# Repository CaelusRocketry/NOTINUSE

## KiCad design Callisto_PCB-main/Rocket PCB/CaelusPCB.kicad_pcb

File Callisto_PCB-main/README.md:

# Callisto_PCB

### Code Description
- `Caelus PCB`: backups of CaelusPCB repo.
- `Comms` (Arduino/Teensy based)
  - `Comms/fakeDataLB/fakeDataLB.ino` generates "fake" 16 switch readings and sends it over UART/Serial communications (LB to GPCB). It also translates each of the switch states into a 4 letter hex string. 
  - `Comms/fakeDataLB/toGPCB.ino` takes the 4 digit hex number send from the UART communications from LB and parses it into 16 integers, which could be 16 valves to swtich.

(there are 16 switches to serve as buffer in the case we wish to expand the number of valves we wish to toggle, although we may not use that many.)

- `Rocket PCB`: KiCad diagrams of the PCB to be placed in the Rocket.

- `twowaycomm` (Raspberry Pi based): testing of wireless two way communications between two Raspberry Pis.
  - `twowaycomm/main0.py` is code to be run on the **sender** Raspberry Pi.
    - **HOWEVER** we may run this on a windows computer for testing, in which case `twowaycomm/main0-ON WIN.py` should be used.
  - `twowaycomm/main1.py` is code to be run on the **receiver** Raspberry Pi, which will send an "acknowledgement" message to the sender raspberry pi.
  - `twowaycomm/main.py` is the combination of `twowaycomm/main0.py` and `twowaycomm/main1.py` into a single file.

The sender Rapsberry Pi represents the Ground Station, and the receiver Raspberry Pi represents the Test Stand or GPCB.

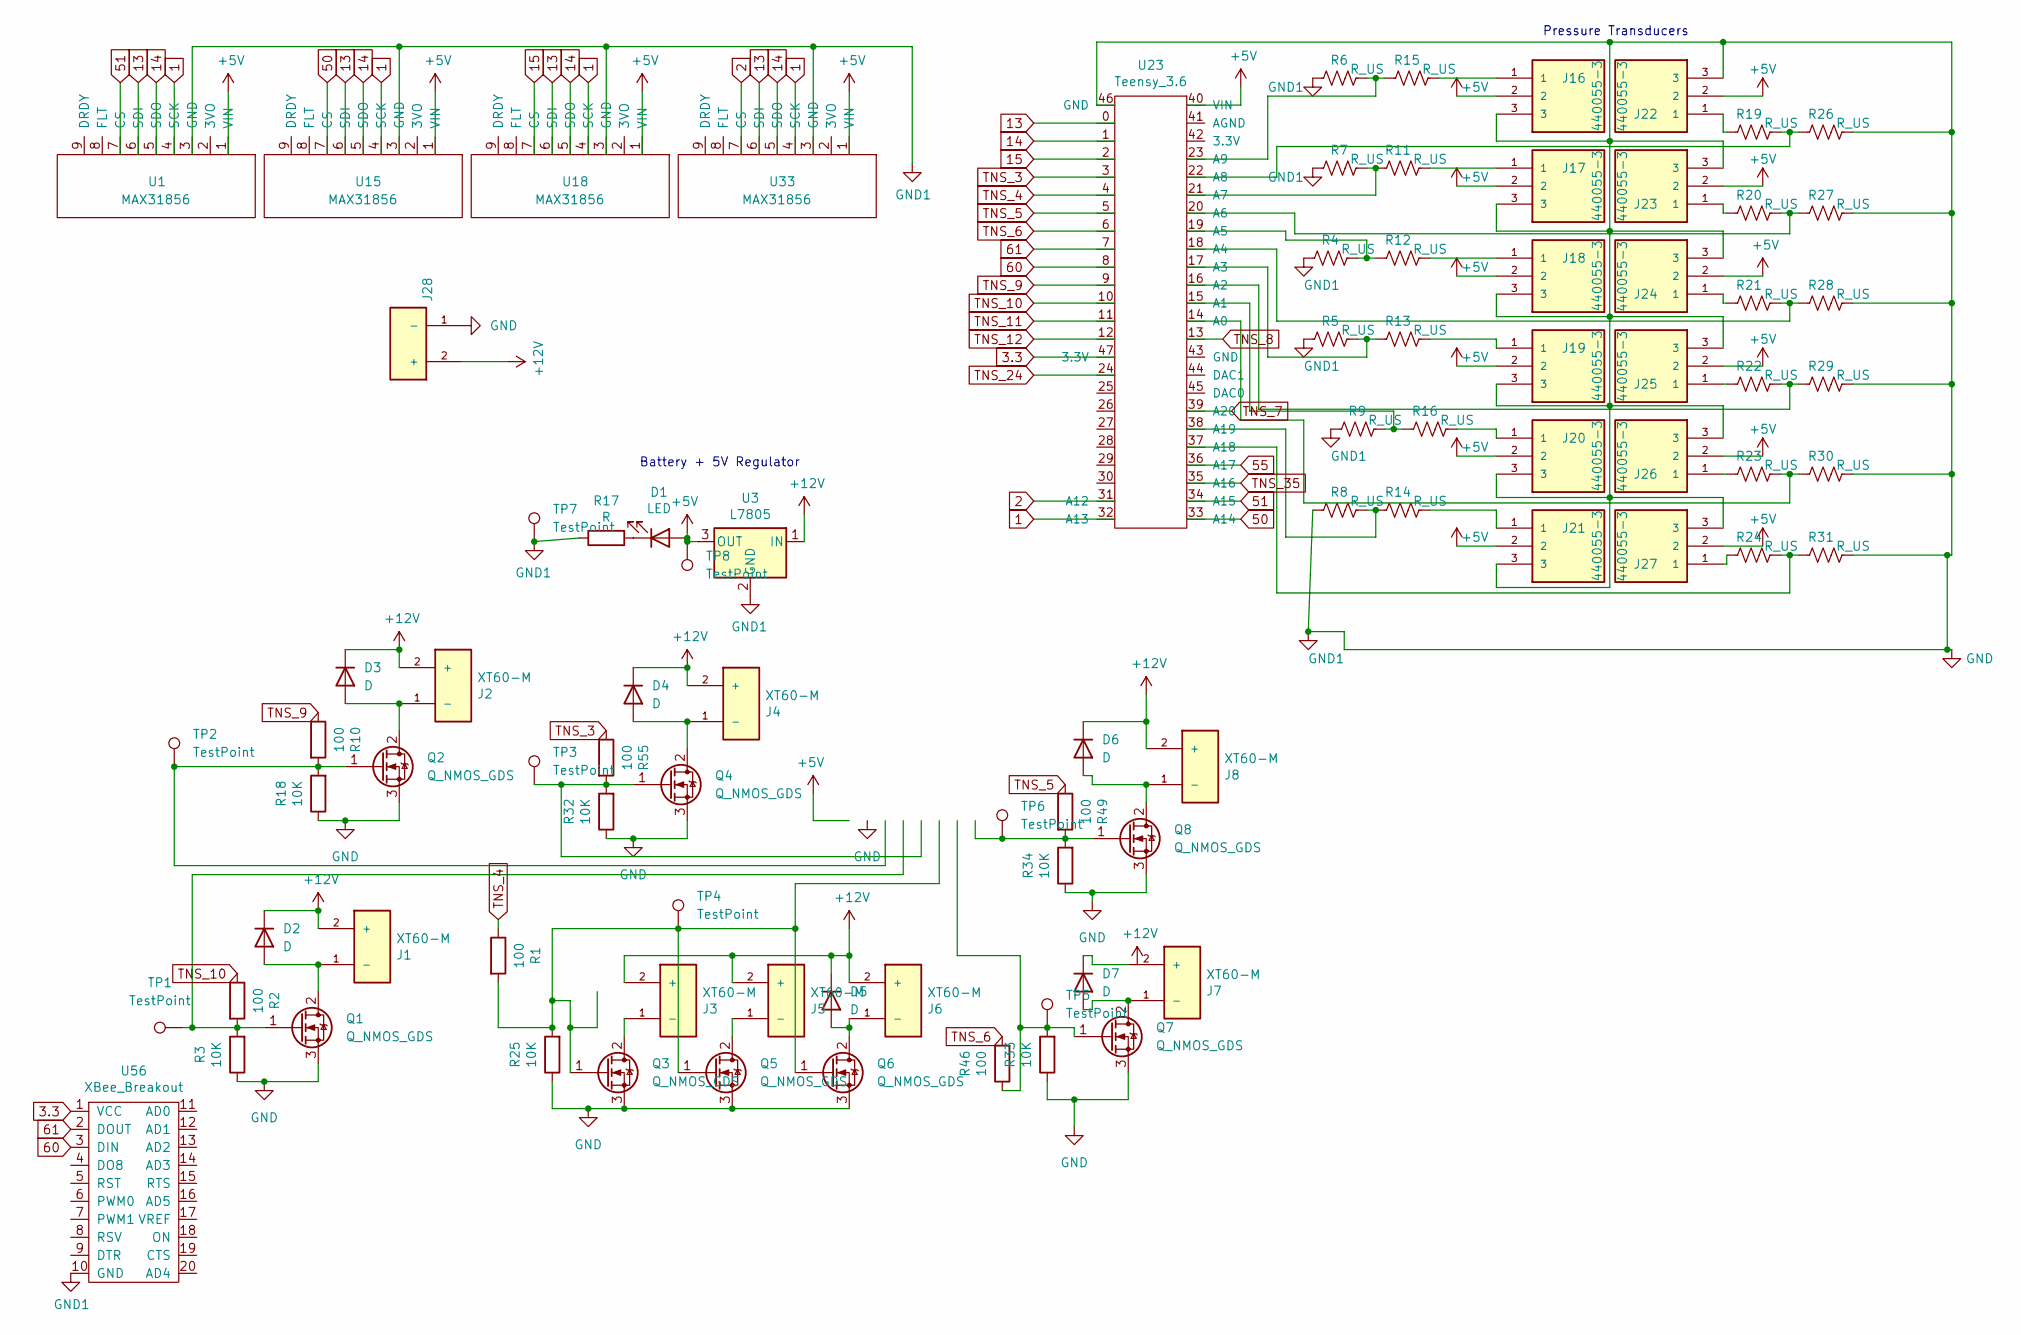
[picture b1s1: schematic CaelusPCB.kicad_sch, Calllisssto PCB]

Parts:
D1: LED; LED_D5.0mm
D2, D3, D4, D5, D6, D7: D; D_A-405_P2.54mm_Vertical_AnodeUp
J1, J2, J3, J4, J5, J6, J7, J8: XT60-M; AMASS_XT60-M; PARTREV 1.2
J16, J17, J18, J19, J20, J21, J22, J23, J24, J25, J26, J27: 440055-3; Crimp_Header
J28: CaelusPCB-rescue_XT60-M-CaelusPCB; AMASS_XT60-M; PARTREV 1.2
Q1, Q2, Q3, Q4, Q5, Q6, Q7, Q8: Q_NMOS_GDS; TO-220-3_Vertical
R1, R2, R10, R46, R49, R55: 100; R_Axial_DIN0309_L9.0mm_D3.2mm_P12.70mm_Horizontal
R3, R18, R25, R32, R33, R34: 10K; R_Axial_DIN0309_L9.0mm_D3.2mm_P12.70mm_Horizontal
R4, R5, R6, R7, R8, R9, R11, R12, R13, R14, R15, R16, R19, R20, R21, R22, R23, R24, R26, R27, R28, R29, R30, R31: R_US; R_Axial_DIN0309_L9.0mm_D3.2mm_P12.70mm_Horizontal
R17: R; R_Axial_DIN0309_L9.0mm_D3.2mm_P12.70mm_Horizontal
TP1, TP2, TP3, TP4, TP5, TP6, TP7, TP8: TestPoint; TestPoint_THTPad_D2.0mm_Drill1.0mm
U1, U15, U18, U33: MAX31856
U3: L7805; TO-220-3_Horizontal_TabDown
U23: Teensy_3.6
U56: XBee_Breakout; Xbee_Breakout

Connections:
1: U1.4 (SCK), U15.4 (SCK), U18.4 (SCK), U23.32 (A13), U33.4 (SCK)
2: U23.31 (A12), U33.7 (CS)
3.3: U23.47 (3.3V), U56.1 (VCC)
13: U1.6 (SDI), U15.6 (SDI), U18.6 (SDI), U23.0, U33.6 (SDI)
14: U1.5 (SDO), U15.5 (SDO), U18.5 (SDO), U23.1, U33.5 (SDO)
15: U18.7 (CS), U23.2
50: U15.7 (CS), U23.33 (A14)
51: U1.7 (CS), U23.34 (A15)
55: U23.36 (A17)
60: U23.8, U56.3 (DIN)
61: U23.7, U56.2 (DOUT)
+5V: D1.2 (A), J16.2, J17.2, J18.2, J19.2, J20.2, J21.2, J22.2, J23.2, J24.2, J25.2, J26.2, J27.2, TP8.1, U1.1 (VIN), U3.3 (OUT), U15.1 (VIN), U18.1 (VIN), U23.40 (VIN), U33.1 (VIN)
+12V: D2.1 (K), D3.1 (K), D4.1 (K), D5.1 (K), D6.1 (K), J1.2 (+), J2.2 (+), J3.2 (+), J4.2 (+), J5.2 (+), J6.2 (+), J8.2 (+), J28.2 (+), U3.1 (IN)
GND: J16.3, J17.3, J18.3, J19.3, J20.3, J21.3, J22.3, J23.3, J24.3, J25.3, J26.3, J27.3, J28.1 (-), Q1.3 (S), Q2.3 (S), Q3.3 (S), Q4.3 (S), Q5.3 (S), Q6.3 (S), Q7.3 (S), Q8.3 (S), R3.1, R4.1, R5.1, R6.1, R7.1, R8.1, R9.1, R17.1, R18.1, R25.1, R26.2, R27.2, R28.2, R29.2, R30.2, R31.2, R32.1, R33.1, R34.1, TP7.1, U1.3 (GND), U3.2 (GND), U15.3 (GND), U18.3 (GND), U23.46 (GND), U33.3 (GND), U56.10 (GND)
unnamed: D1.1 (K), R17.2
unnamed: D2.2 (A), J1.1 (-), Q1.2 (D)
unnamed: D3.2 (A), J2.1 (-), Q2.2 (D)
unnamed: D4.2 (A), J4.1 (-), Q4.2 (D)
unnamed: D5.2 (A), J6.1 (-), Q6.2 (D)
unnamed: D6.2 (A), J8.1 (-), Q8.2 (D)
unnamed: D7.1 (K), J7.2 (+)
unnamed: D7.2 (A), J7.1 (-), Q7.2 (D)
unnamed: J3.1 (-), Q3.2 (D)
unnamed: J5.1 (-), Q5.2 (D)
unnamed: J16.1, R15.2
unnamed: J17.1, R11.2
unnamed: J18.1, R12.2
unnamed: J19.1, R13.2
unnamed: J20.1, R16.2
unnamed: J21.1, R14.2
unnamed: J22.1, R19.1
unnamed: J23.1, R20.1
unnamed: J24.1, R21.1
unnamed: J25.1, R22.1
unnamed: J26.1, R23.1
unnamed: J27.1, R24.1
unnamed: Q1.1 (G), R2.2, R3.2, TP1.1
unnamed: Q2.1 (G), R10.2, R18.2, TP2.1
unnamed: Q3.1 (G), Q5.1 (G), Q6.1 (G), R1.2, R25.2, TP4.1
unnamed: Q4.1 (G), R32.2, R55.2, TP3.1
unnamed: Q7.1 (G), R33.2, R46.1, TP5.1
unnamed: Q8.1 (G), R34.2, R49.2, TP6.1
unnamed: R7.2, R11.1, U23.21 (A7)
unnamed: R4.2, R12.1, U23.19 (A5)
unnamed: R5.2, R13.1, U23.17 (A3)
unnamed: R8.2, R14.1, U23.38 (A19)
unnamed: R6.2, R15.1, U23.23 (A9)
unnamed: R9.2, R16.1, U23.15 (A1)
unnamed: R19.2, R26.1, U23.22 (A8)
unnamed: R20.2, R27.1, U23.20 (A6)
unnamed: R21.2, R28.1, U23.18 (A4)
unnamed: R22.2, R29.1, U23.16 (A2)
unnamed: R23.2, R30.1, U23.14 (A0)
unnamed: R24.2, R31.1, U23.37 (A18)
TNS_3: R55.1, U23.3
TNS_4: R1.1, U23.4
TNS_5: R49.1, U23.5
TNS_6: R46.2, U23.6
TNS_7: U23.39 (A20)
TNS_8: U23.13
TNS_9: R10.1, U23.9
TNS_10: R2.1, U23.10
TNS_11: U23.11
TNS_12: U23.12
TNS_24: U23.24
TNS_35: U23.35 (A16)

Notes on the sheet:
Battery + 5V Regulator
Pressure Transducers

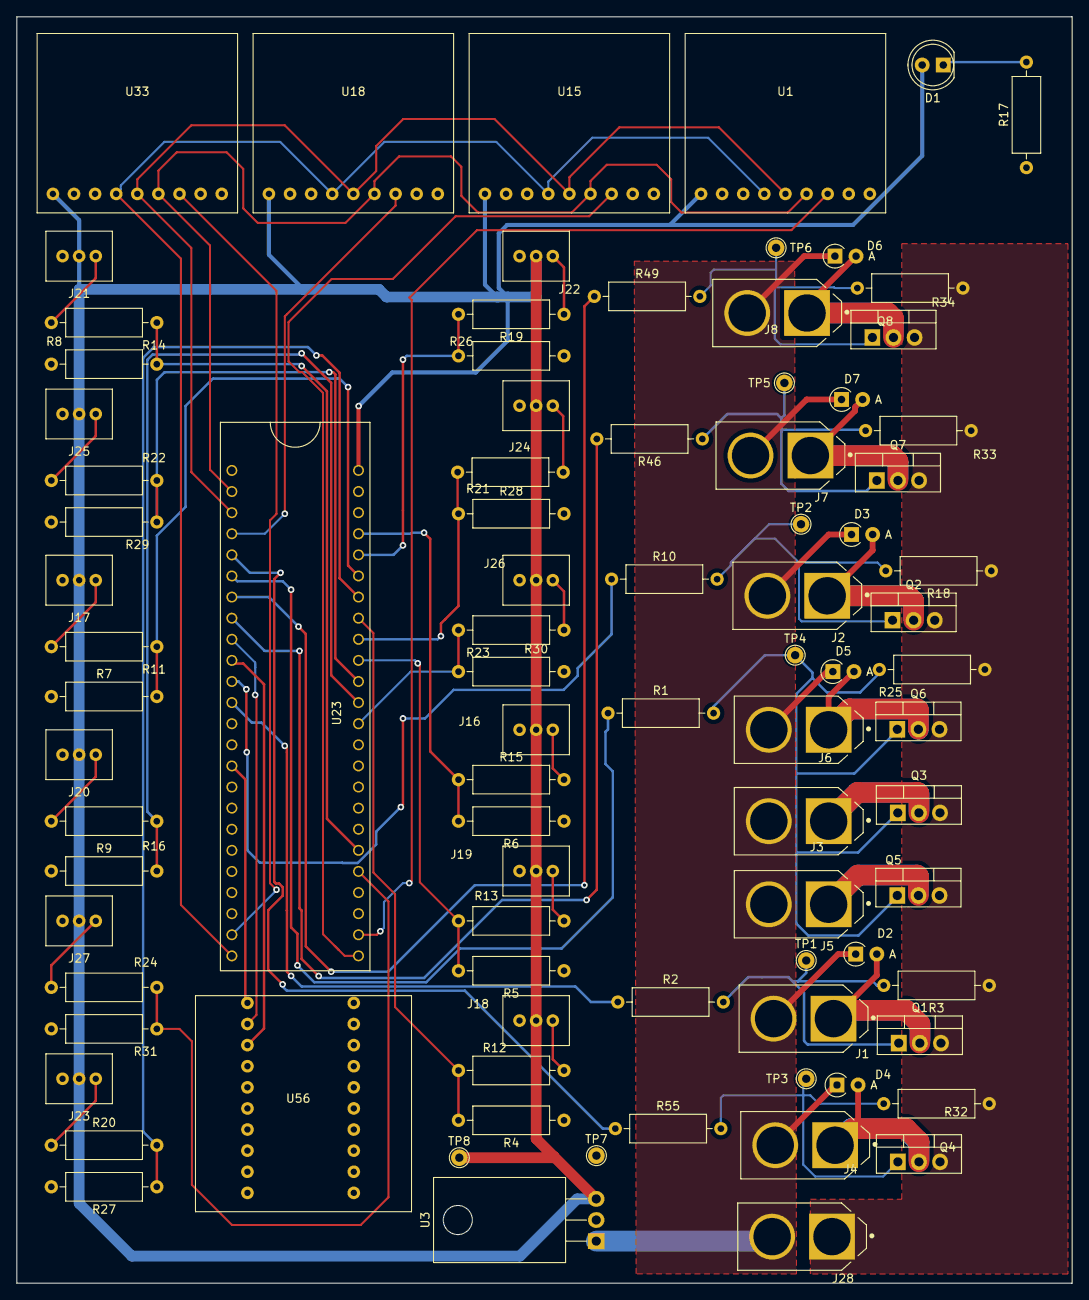
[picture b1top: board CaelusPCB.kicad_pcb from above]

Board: 4 copper layers, 127.0 x 152.4 mm, 88 parts (0 on the bottom side), 59 nets.

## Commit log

2025-06-07 new stuff
    ..
2025-06-07 more stuf
    ...
2025-06-07 design liquid engine main
2025-06-07 new stuf
    ...
2025-06-07 new
    ...
2025-06-07 new
    ..
2025-06-07 new stuf
